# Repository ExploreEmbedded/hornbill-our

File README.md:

# hornbill-our
Open Universal Remote with Hornbill ESP32 dev tools. BLE IR Bridge for device control. This is demonstration of what is possible with Hornbill ESP32 platform. To know more and support our work visit:
https://www.crowdsupply.com/explore-embedded/hornbill
 </img>

#ToDo
If there is enough interest in the project, we would like to add the following features:
<ul>
<li>
 Add other major IR protocols. At least the once supported by IRRemote Arduino Library 
</li>
<li>
Integrate Irdb.tk api so that remotes can be add to the app during the setup. This would require internet connection only during setup. 
</li>

<li>
RemoteMaker: Add app/firmware feature to create remotes that are not available in the database.
</li>

</ul>

If you've anyother suggestions that could be helpful, please raise on issue here on the repo. 
 
# App Screens
 </img>
 </img>
 </img>

 </img>
 </img>
 </img>

 </img>
 </img>

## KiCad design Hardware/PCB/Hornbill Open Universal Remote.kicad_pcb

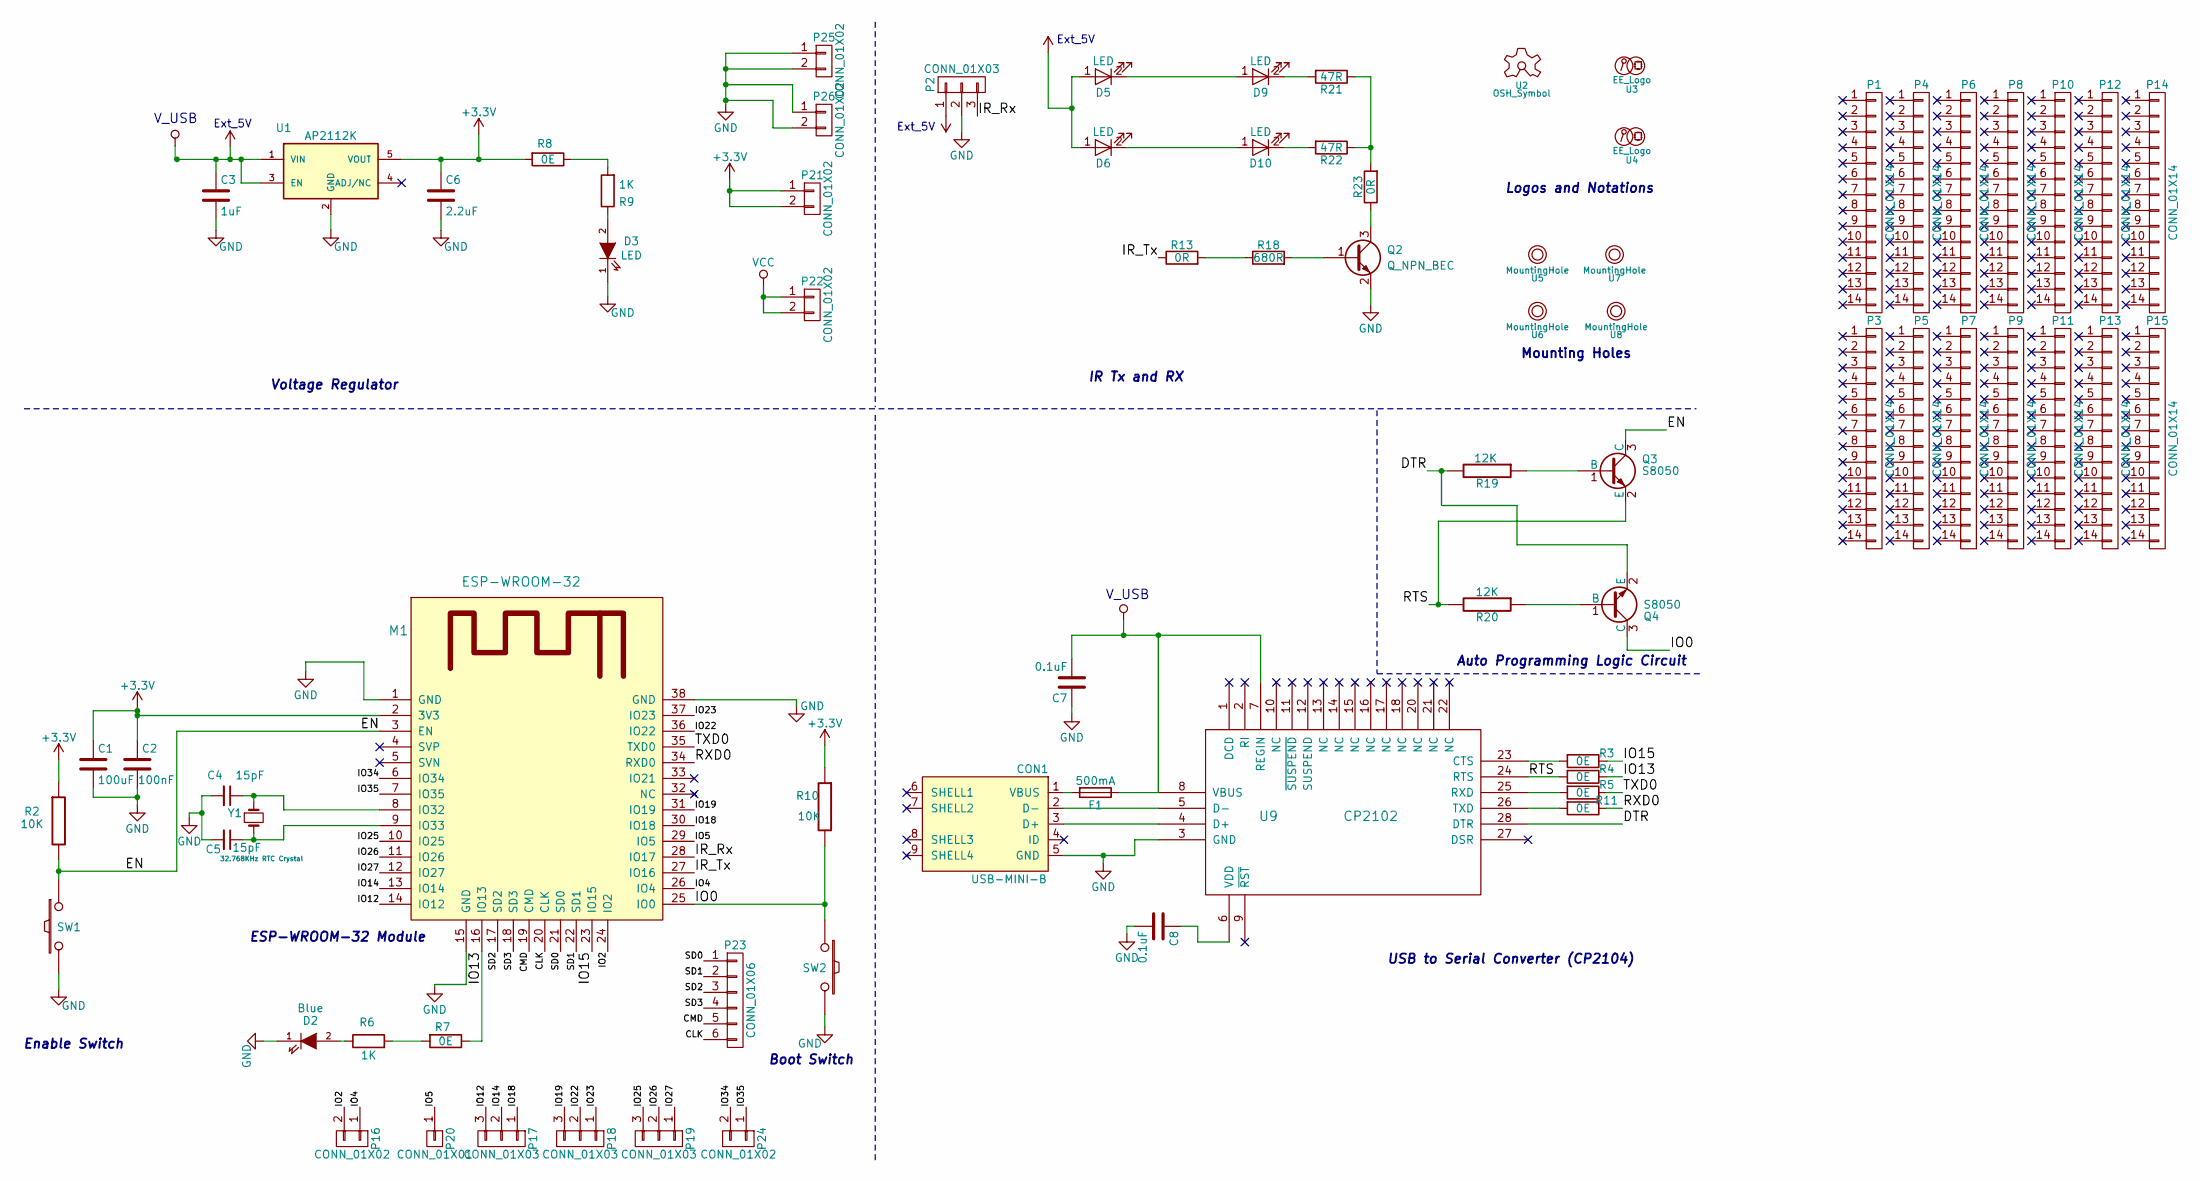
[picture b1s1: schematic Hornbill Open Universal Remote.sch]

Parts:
C1: 100uF; C_1206
C2: 100nF; C_0603
C3: 1uF; C_0603
C4, C5: 15pF; C_0603
C6: 2.2uF; C_0603
C7, C8: 0.1uF; C_0603
CON1: USB-MINI-B; USB_Micro-B_SMD_NEW_1
D2: Blue; LED-0603_NEW
D3: LED; LED-0603_NEW
D5, D6, D9, D10: LED; LED-5MM
F1: 500mA; Fuse_500mA
M1: ESP-WROOM-32; ESP-32S
P1, P3, P4, P5, P6, P7, P8, P9, P10, P11, P12, P13, P14, P15: CONN_01X14; EE_Pin_Header_Straight_1x14_Pitch2.54mm
P2, P17, P18, P19: CONN_01X03; Pin_Header_Straight_1x03_Pitch2.54mm
P16, P24, P25, P26: CONN_01X02; Pin_Header_Straight_1x02_Pitch2.54mm
P20: CONN_01X01; Pin_Header_Straight_1x01_Pitch2.54mm
P21, P22: CONN_01X02; Pin_Header_Straight_2x01_Pitch2.54mm
P23: CONN_01X06; Pin_Header_Straight_1x06_Pitch2.54mm
Q2: Q_NPN_BEC; SOT-23
Q3, Q4: S8050; SOT-23
R2, R10: 10K; R_0603
R3, R4, R5, R7, R8, R11: 0E; R_0603
R6, R9: 1K; R_0603
R13, R23: 0R; R_0603
R18: 680R; R_0603
R19, R20: 12K; R_0603
R21, R22: 47R; R_0603
SW1, SW2: SW_PUSH; smd_push2_New
U1: AP2112K; SOT-23-5
U2: OSH_Symbol; Logo_silk_OSHW_6x6mm
U3: EE_Logo; Hornbill_OUR
U4: EE_Logo; Logo_8
U5, U6, U7, U8: MountingHole; MountingHole_2.5mm
U9: CP2102; cp2102_xl2
Y1: 32.768KHz RTC Crystal; SMD_RTC_Crstl

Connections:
+3V3: C1.1, C2.1, C6.1, M1.2 (3V3), P21.1, P21.2, R2.1, R8.2, R10.1, U1.5 (VOUT)
+5V: C3.1, C7.2, D5.1 (A), D6.1 (A), F1.1, P2.1, P22.1, P22.2, U1.1 (VIN), U1.3 (EN), U9.7 (REGIN), U9.8 (VBUS)
/CLK: M1.20 (CLK), P23.6
/CMD: M1.19 (CMD), P23.5
/DTR: Q4.2 (E), R19.2, U9.28 (DTR)
/EN: M1.3 (EN), Q3.3 (C), R2.2, SW1.1
/IO0: M1.25 (IO0), Q4.3 (C), R10.2, SW2.1
/IO2: M1.24 (IO2), P16.2
/IO4: M1.26 (IO4), P16.1
/IO5: M1.29 (IO5), P20.1
/IO12: M1.14 (IO12), P17.3
/IO13: M1.16 (IO13), R4.1, R7.1
/IO14: M1.13 (IO14), P17.2
/IO15: M1.23 (IO15), R3.1
/IO18: M1.30 (IO18), P17.1
/IO19: M1.31 (IO19), P18.3
/IO22: M1.36 (IO22), P18.2
/IO23: M1.37 (IO23), P18.1
/IO25: M1.10 (IO25), P19.3
/IO26: M1.11 (IO26), P19.2
/IO27: M1.12 (IO27), P19.1
/IO34: M1.6 (IO34), P24.2
/IO35: M1.7 (IO35), P24.1
/IR_Rx: M1.28 (IO17), P2.3
/IR_Tx: M1.27 (IO16), R13.1
/RTS: Q3.2 (E), R4.2, R20.2, U9.24 (RTS)
/RXD0: M1.34 (RXD0), R11.1
/SD0: M1.21 (SD0), P23.1
/SD1: M1.22 (SD1), P23.2
/SD2: M1.17 (SD2), P23.3
/SD3: M1.18 (SD3), P23.4
/TXD0: M1.35 (TXD0), R5.1
GND: C1.2, C2.2, C3.2, C4.2, C5.2, C6.2, C7.1, C8.2, CON1.5 (GND), D2.1 (K), D3.1 (K), M1.1 (GND), M1.15 (GND), M1.38 (GND), P2.2, P25.1, P25.2, P26.1, P26.2, Q2.2 (E), SW1.2, SW2.2, U1.2 (GND), U9.3 (GND)
unnamed: C4.1, M1.8 (IO32), Y1.1
unnamed: C5.1, M1.9 (IO33), Y1.2
unnamed: C8.1, U9.6 (VDD)
unnamed: CON1.1 (VBUS), F1.2
unnamed: CON1.2 (D-), U9.5 (D-)
unnamed: CON1.3 (D+), U9.4 (D+)
unnamed: D2.2 (A), R6.1
unnamed: D3.2 (A), R9.1
unnamed: D5.2 (K), D9.1 (A)
unnamed: D9.2 (K), R21.2
unnamed: D6.2 (K), D10.1 (A)
unnamed: D10.2 (K), R22.2
unnamed: Q2.1 (B), R18.2
unnamed: Q2.3 (C), R23.1
unnamed: Q3.1 (B), R19.1
unnamed: Q4.1 (B), R20.1
unnamed: R3.2, U9.23 (CTS)
unnamed: R5.2, U9.25 (RXD)
unnamed: R6.2, R7.2
unnamed: R8.1, R9.2
unnamed: R11.2, U9.26 (TXD)
unnamed: R13.2, R18.1
unnamed: R21.1, R22.1, R23.2

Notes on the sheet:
Logos and Notations
Enable Switch
IR Tx and RX
Boot Switch
V_USB
Ext_5V
Voltage Regulator
Auto Programming Logic Circuit
ESP-WROOM-32 Module
USB to Serial Converter (CP2104)
Mounting Holes

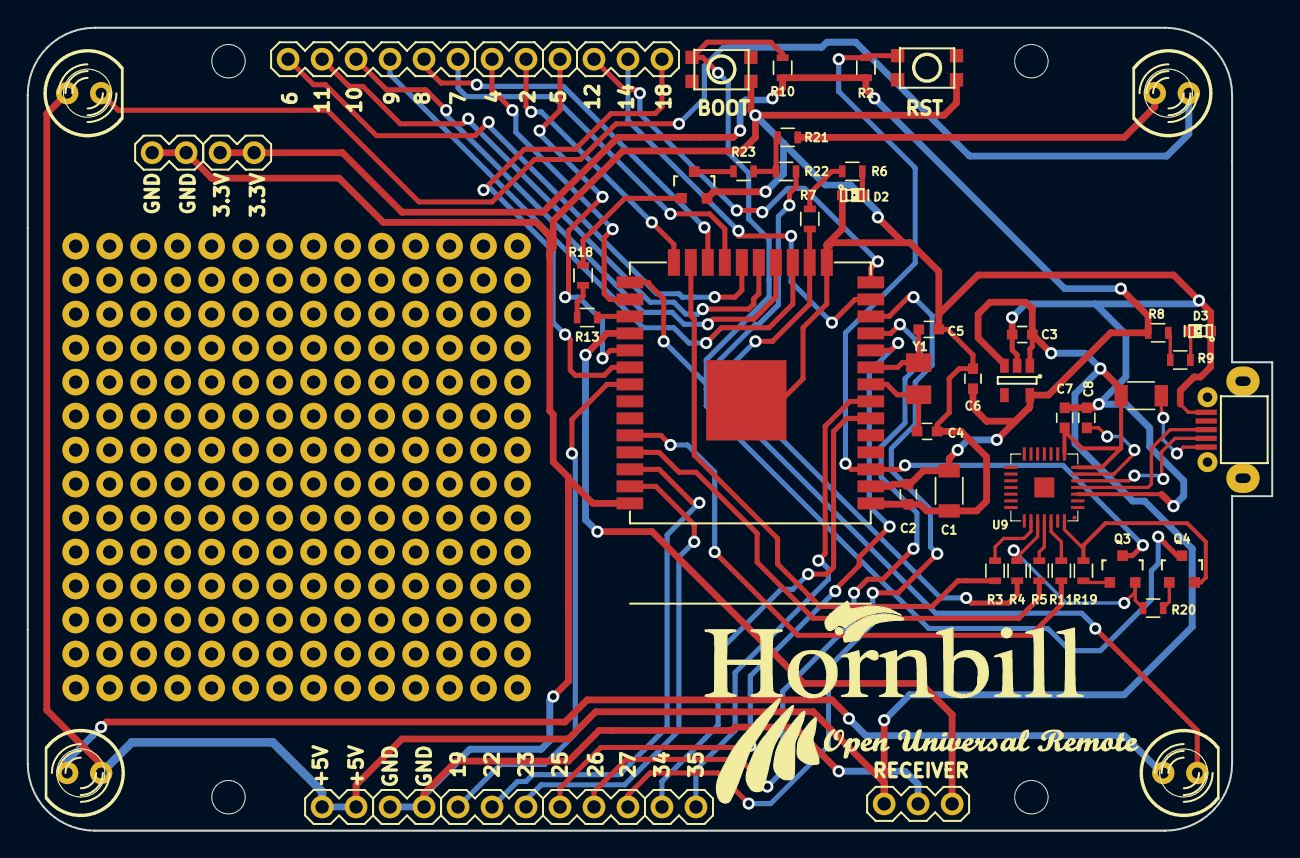
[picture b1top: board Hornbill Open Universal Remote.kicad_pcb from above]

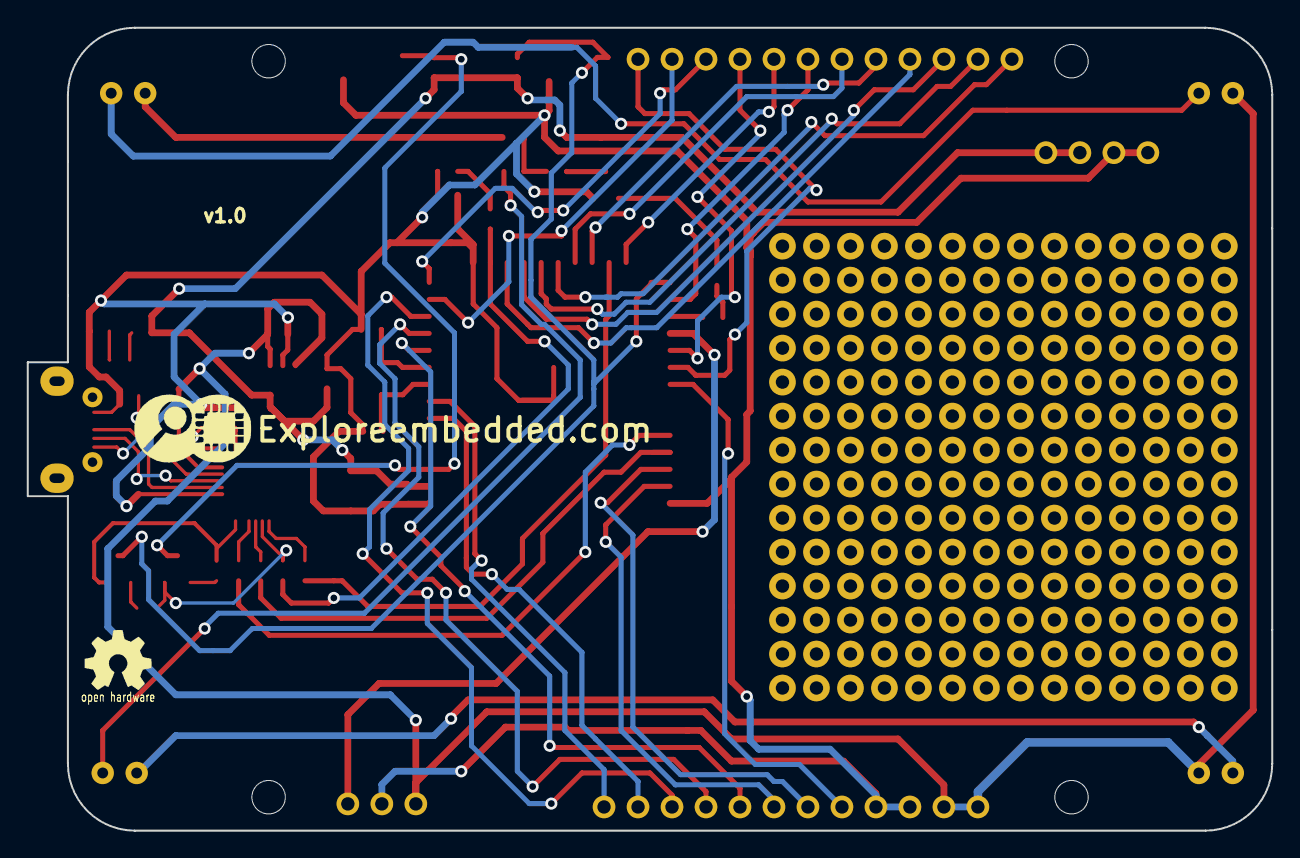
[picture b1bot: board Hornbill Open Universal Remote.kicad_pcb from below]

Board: 2 copper layers, 93.0 x 60.0 mm, 75 parts (2 on the bottom side), 56 nets.

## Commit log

2017-02-23 initial working version of the app
2017-02-24 gui for DTH remote, data source added in format compatible with irdb.tk website
2017-02-24 added home theatre intex gui and codes
2017-02-25 support for tv remote
2017-02-27 tv keys recorded firmware test code
2017-03-01 firmware for nec
2017-03-01 demo complete, TV, music, DTH all work
2017-03-02 screen shots of the app
2017-03-02 add app screen shots
    add app screen shots
2017-03-03 fixed dth ch+ crash
2017-03-04 minor changes and the first pic
2017-04-06 Added Design Files
2017-05-01 Hornbill logo added for OUR
2017-06-07 BOM,process sheet added
2017-08-14 added BLE test code
2017-08-17 BLE and pronto implementation
2017-08-21 Used esp32 RMT for sending the IR codes. Renamed the old hornbill firmare folder.
2017-08-24 Added support for different Tx frequency
    Added support for different Tx frequency without doing rmt driver
    install and uninstall each time.
    Also changed code to fix IR Tx freq issue.
2017-09-07 typo
2017-09-20 IO pins taken out
2017-09-21 PCB legends renamed and gerber file generated
2017-09-23 Updated esp32_rmt files to fix timing issues
    Also removed redudant code
2017-09-27 Legend modified and gerber file generated
